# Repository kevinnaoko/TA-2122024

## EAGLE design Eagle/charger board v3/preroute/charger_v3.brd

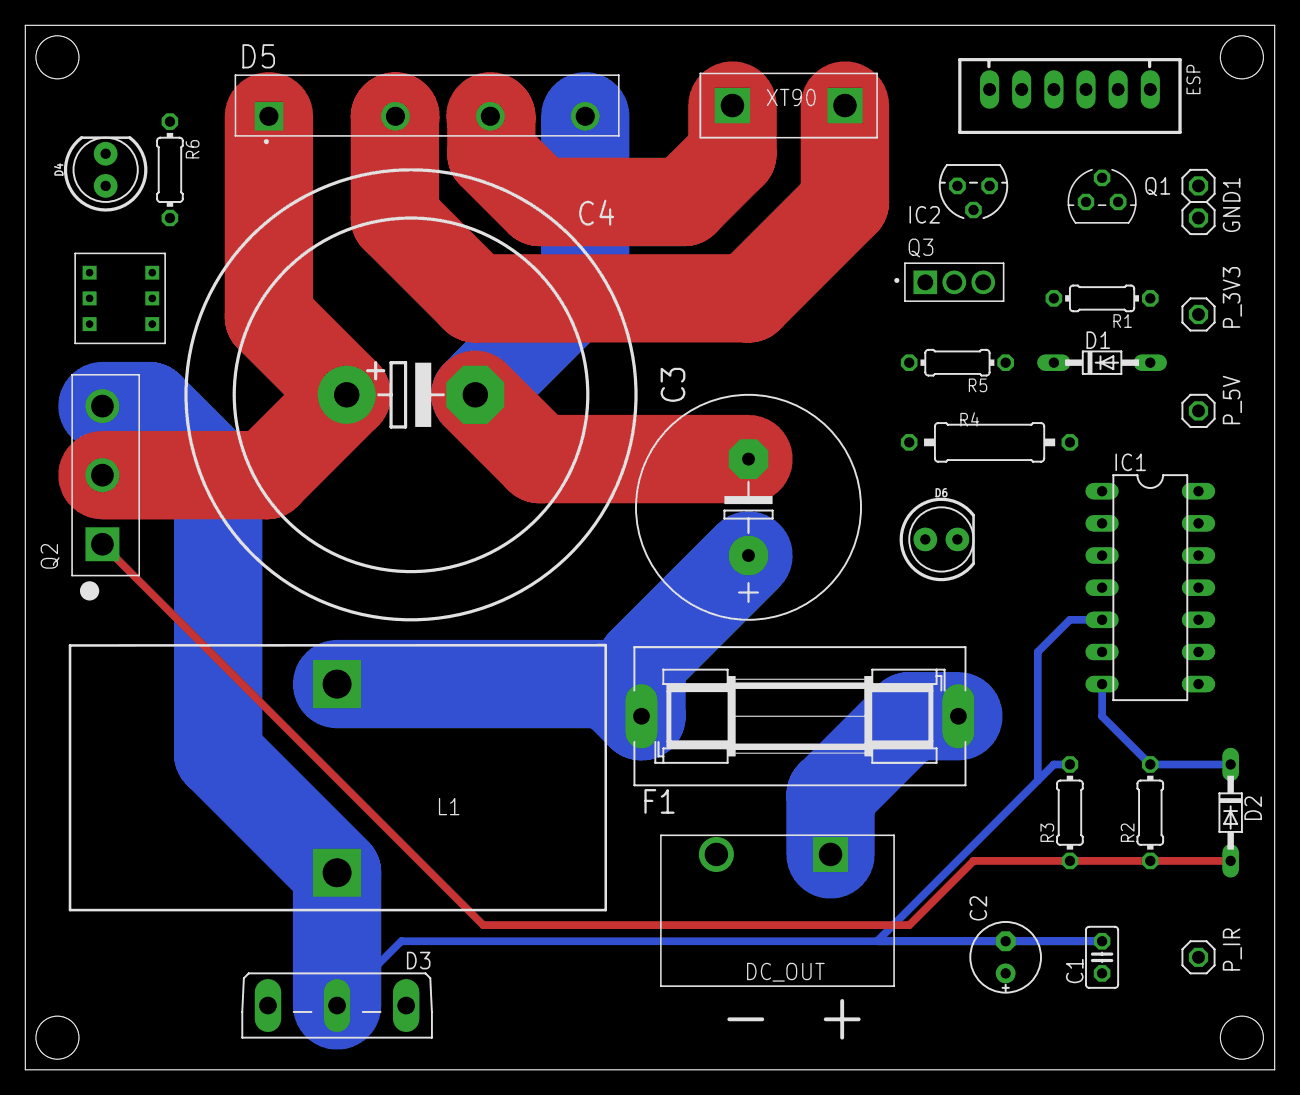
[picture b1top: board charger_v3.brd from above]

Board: 2 copper layers, 98.7 x 82.5 mm, 32 parts (0 on the bottom side), 21 nets.

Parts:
AC_IN: XT90A; XT90-PAD
C1: 100nF; C025-025X050
C2: 22uF; E2,5-6E
C3: 150uF; E7,5-18
C4: 470uF; EB35D
D1, D2: UF4007; DO34-7
D3: PBYR3035; SOT93S
D4, D6: LED_5MM
D5: GBJ3510-BP; DIOB_GBJ3510-BP
DC_OUT: 1977477-2; TE_1977477-2
ESP: JST-XH-06-PIN-LONG-PAD; JST-XH-06-PACKAGE-LONG-PAD
F1: SH25
GND1, GND2: 1X01
IC1: IR2110D; DIL14
IC2: LM35CZ; TO92
L1: 1mH; TJ7-U1
P_3V3, P_5V: 1X01
P_IR: 1X01
Q1: 2N7000; TO92
Q2: IRFP240; TO247AC
Q3: MJE13003G; TO229P780X300X1364-3
R1, R6: 10k; 0204/7
R2: 10; 0204/7
R3: 1k; 0204/7
R4: 68k; 0309/12
R5: 2.7k; 0204/7
U$1: SWITCH-DPDT-7X7A; TL-2230

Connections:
5V: ESP.2, IC1.9, IC2.1, R1.2
12V: D1.A, ESP.1, IC1.3
AC_1: AC_IN.P$1, D5.2
AC_2: AC_IN.P$2, D5.3
GND: C3.-, C4.-, D3.A1, D5.4, DC_OUT.2, ESP.6, GND1.1, GND2.1, IC1.2, IC1.11, IC1.12, IC1.13, IC2.3, Q1.1, Q3.3, R6.2
HVDC: C4.+, D5.1, Q2.2, U$1.1
unnamed: D2.C, IC1.7, R2.2
unnamed: D4.A, U$1.2
unnamed: Q3.2, R4.1
unnamed: D6.K, R4.2
unnamed: Q3.1, R5.2
unnamed: D4.K, R6.1
NMOS_SOURCE: C1.2, C2.-, D3.C, IC1.5, L1.1, Q2.3, R3.2
PWM_5V: IC1.10, P_5V.1, Q1.3, R1.1
PWM_12V: D2.A, P_IR.1, Q2.1, R2.1, R3.1
PWM_SW1: ESP.3, P_3V3.1, Q1.2
PWM_SW2: ESP.4, R5.1
TEMP: ESP.5, IC2.2
VB: C1.1, C2.+, D1.C, IC1.6
V_OUT: C3.+, D6.A, F1.1, L1.2
V_OUT_FUSE: DC_OUT.1, F1.2

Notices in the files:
parts and their libraries:
Sparkfun_LED: Licensing: Creative Commons ShareAlike 4.0 International - https://creativecommons.org/licenses/by-sa/4.0
